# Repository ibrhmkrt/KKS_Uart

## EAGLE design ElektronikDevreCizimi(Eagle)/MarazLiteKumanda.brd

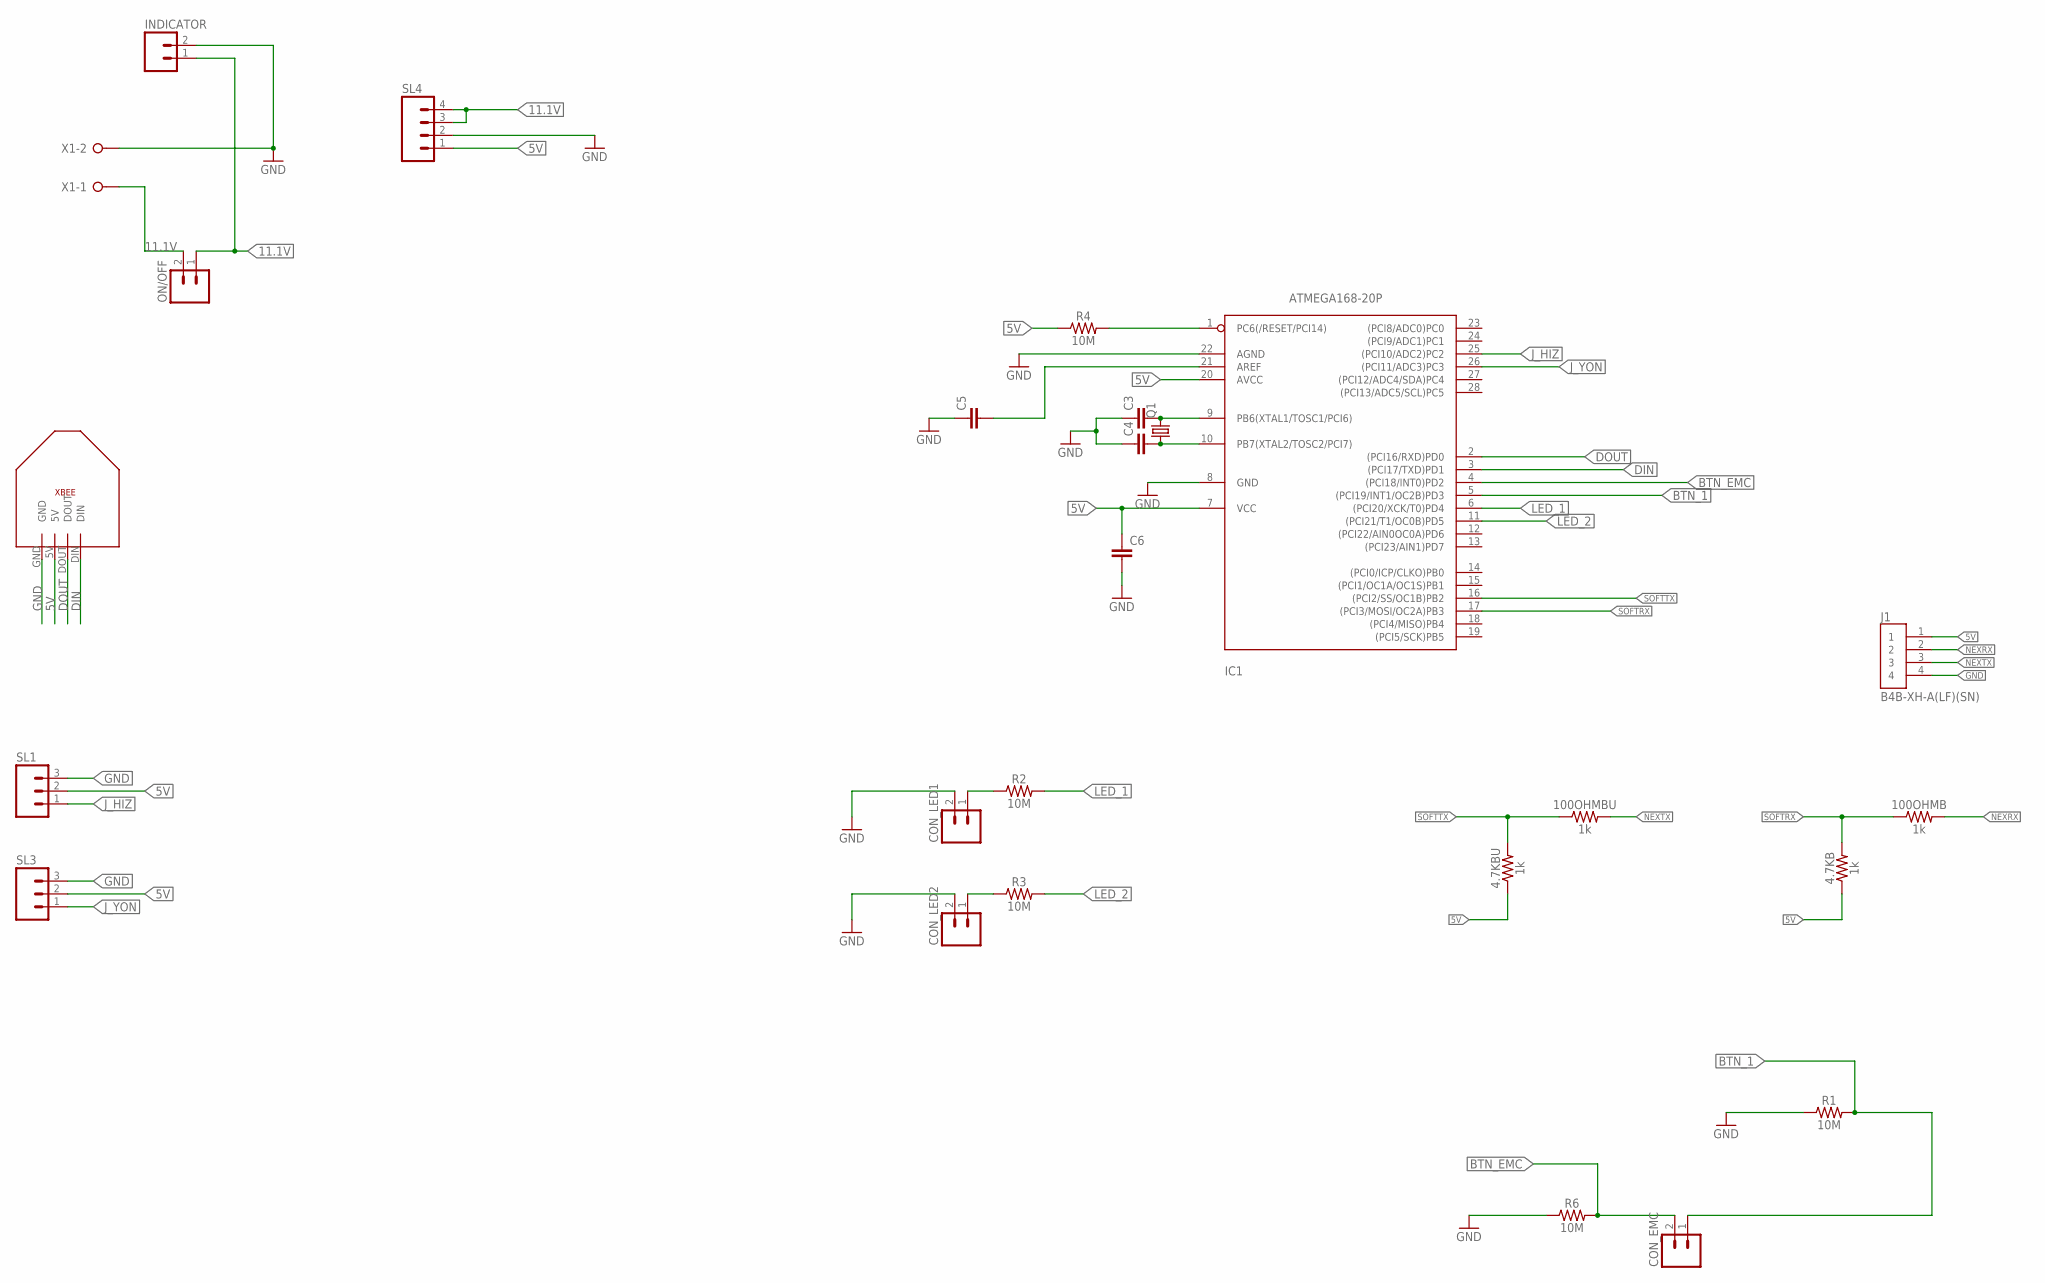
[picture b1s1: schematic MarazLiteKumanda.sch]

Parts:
4.7KB, 4.7KBU, 100OHMB, 100OHMBU: 1k; AXIAL-0.3
C3, C4, C5, C6: C2.5/2; C2.5-2
CON_EMC: M02; 02P
CON_LED1, CON_LED2: M02; 02P
IC1: ATMEGA168-20P; DIL28-3
INDICATOR: M02; 02P
J1: B4B-XH-A(LF)(SN); JST_B4B-XH-A(LF)(SN)
ON/OFF: M02; 02P
Q1: CRYSTALHC49U-V; HC49U-V
R1, R2, R3, R4, R6: 10M; AXIAL-0.3
SL1, SL3: M03; 03P
SL4: M04; 04P
U$1: XBEE
X1: W237-02P; W237-132

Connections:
5V: 4.7KB.P$1 (1), 4.7KBU.P$1 (1), C6.1, IC1.7 (VCC), IC1.20 (AVCC), J1.1, R4.P$1 (1), SL1.2, SL3.2, SL4.1, U$1.5V
11.1V: INDICATOR.1, ON/OFF.1, ON/OFF.2, SL4.3, SL4.4, X1.1
BTN_1: CON_EMC.1, IC1.5 ((PCI19/INT1/OC2B)PD3), R1.P$2 (2)
BTN_EMC: CON_EMC.2, IC1.4 ((PCI18/INT0)PD2), R6.P$2 (2)
DIN: IC1.3 ((PCI17/TXD)PD1), U$1.DIN
DOUT: IC1.2 ((PCI16/RXD)PD0), U$1.DOUT
GND: C3.1, C4.1, C5.1, C6.2, CON_LED1.2, CON_LED2.2, IC1.8 (GND), IC1.22 (AGND), INDICATOR.2, J1.4, R1.P$1 (1), R6.P$1 (1), SL1.3, SL3.3, SL4.2, U$1.GND, X1.2
J_HIZ: IC1.25 ((PCI10/ADC2)PC2), SL1.1
J_YON: IC1.26 ((PCI11/ADC3)PC3), SL3.1
LED_1: IC1.6 ((PCI20/XCK/T0)PD4), R2.P$2 (2)
LED_2: IC1.11 ((PCI21/T1/OC0B)PD5), R3.P$2 (2)
unnamed: C5.2, IC1.21 (AREF)
unnamed: CON_LED2.1, R3.P$1 (1)
unnamed: CON_LED1.1, R2.P$1 (1)
unnamed: C3.2, IC1.9 (PB6(XTAL1/TOSC1/PCI6)), Q1.2
unnamed: C4.2, IC1.10 (PB7(XTAL2/TOSC2/PCI7)), Q1.1
unnamed: IC1.1 (PC6(/RESET/PCI14)), R4.P$2 (2)
NEXRX: 100OHMB.P$2 (2), J1.2
NEXTX: 100OHMBU.P$2 (2), J1.3
SOFTRX: 4.7KB.P$2 (2), 100OHMB.P$1 (1), IC1.17 ((PCI3/MOSI/OC2A)PB3)
SOFTTX: 4.7KBU.P$2 (2), 100OHMBU.P$1 (1), IC1.16 ((PCI2/SS/OC1B)PB2)

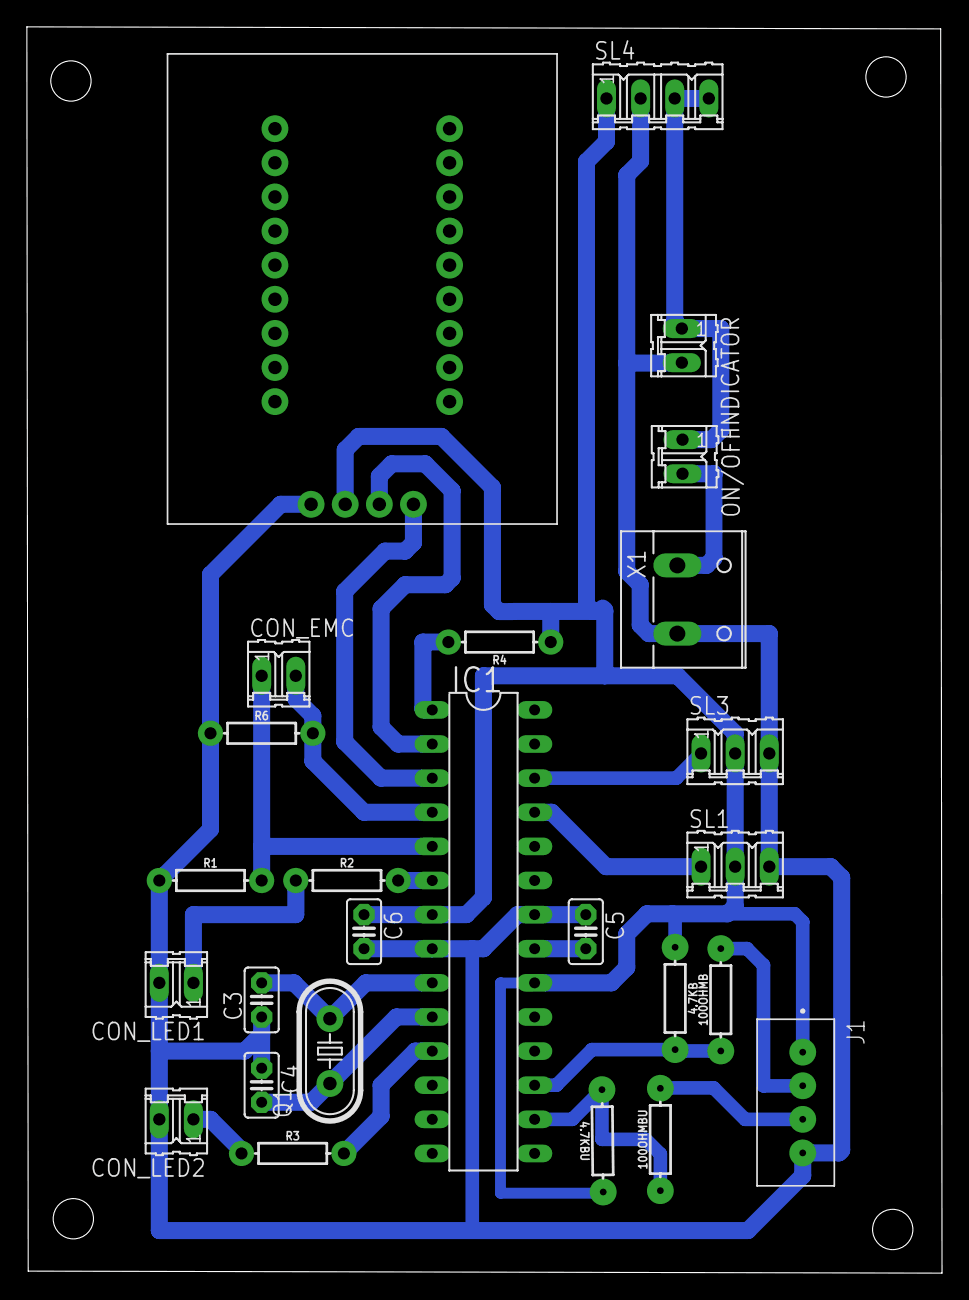
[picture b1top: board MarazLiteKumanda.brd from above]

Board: 2 copper layers, 68.1 x 92.8 mm, 26 parts (0 on the bottom side), 21 nets.

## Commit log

2020-10-17 Final

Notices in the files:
parts and their libraries:
SparkFun-Resistors: Licensing: Creative Commons ShareAlike 4.0 International - https://creativecommons.org/licenses/by-sa/4.0
